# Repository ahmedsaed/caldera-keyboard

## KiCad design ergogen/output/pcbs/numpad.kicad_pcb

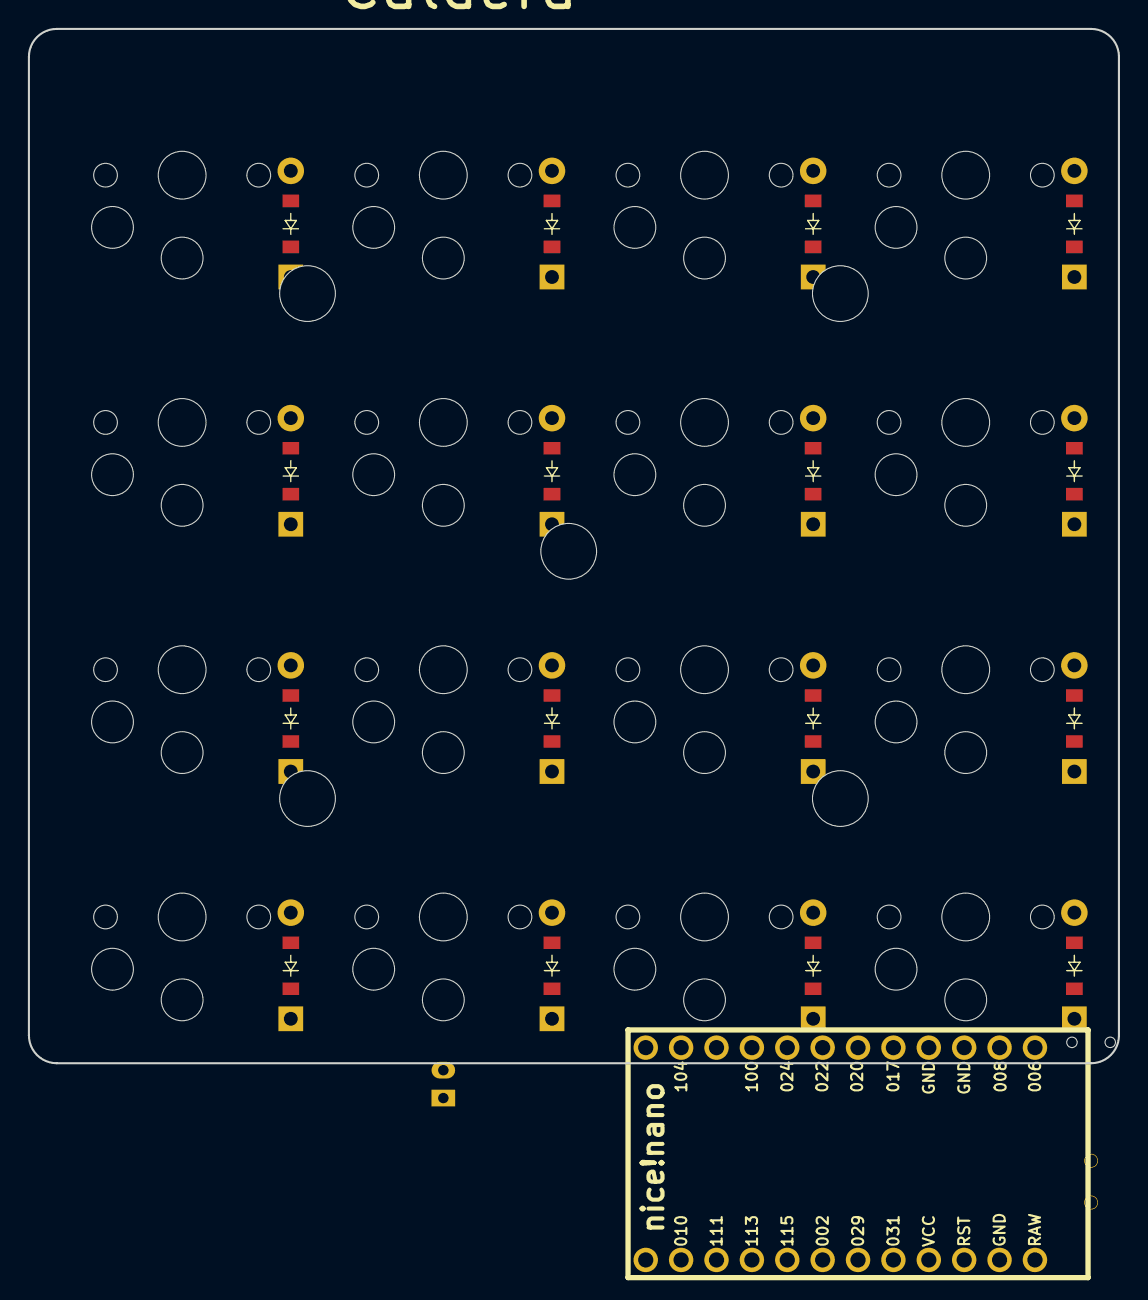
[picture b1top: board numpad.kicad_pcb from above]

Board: 2 copper layers, 78.2 x 74.2 mm, 36 parts (0 on the bottom side), 28 nets, no tracks yet.

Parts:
B1: Panasonic_EVQPUL_EVQPUC
D1, D2, D3, D4, D5, D6, D7, D8, D9, D10, D11, D12, D13, D14, D15, D16: ComboDiode
JST1: JST_PH_S2B-PH-K_02x2.00mm_Angled
MCU1: nice_nano
S1, S2, S3, S4, S5, S6, S7, S8, S9, S10, S11, S12, S13, S14, S15, S16: PG1350
T1: SPDT_C128955

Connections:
GND: B1.1, JST1.2, MCU1.3, MCU1.4, MCU1.23
P002: D3.1, D7.1, D11.1, D15.1, MCU1.18
P020: MCU1.6, S1.1, S2.1, S3.1, S4.1
P022: MCU1.7, S5.1, S6.1, S7.1, S8.1
P024: MCU1.8, S9.1, S10.1, S11.1, S12.1
P029: D4.1, D8.1, D12.1, D16.1, MCU1.19
P100: MCU1.9, S13.1, S14.1, S15.1, S16.1
P113: D1.1, D5.1, D9.1, D13.1, MCU1.16
P115: D2.1, D6.1, D10.1, D14.1, MCU1.17
RAW: MCU1.24, T1.2
RST: B1.2, MCU1.22
col0_row0: D1.2, S1.2
col0_row1: D2.2, S2.2
col0_row2: D3.2, S3.2
col0_row3: D4.2, S4.2
col1_row0: D5.2, S5.2
col1_row1: D6.2, S6.2
col1_row2: D7.2, S7.2
col1_row3: D8.2, S8.2
col2_row0: D9.2, S9.2
col2_row1: D10.2, S10.2
col2_row2: D11.2, S11.2
col2_row3: D12.2, S12.2
col3_row0: D13.2, S13.2
col3_row1: D14.2, S14.2
col3_row2: D15.2, S15.2
col3_row3: D16.2, S16.2
pos: JST1.1, T1.1

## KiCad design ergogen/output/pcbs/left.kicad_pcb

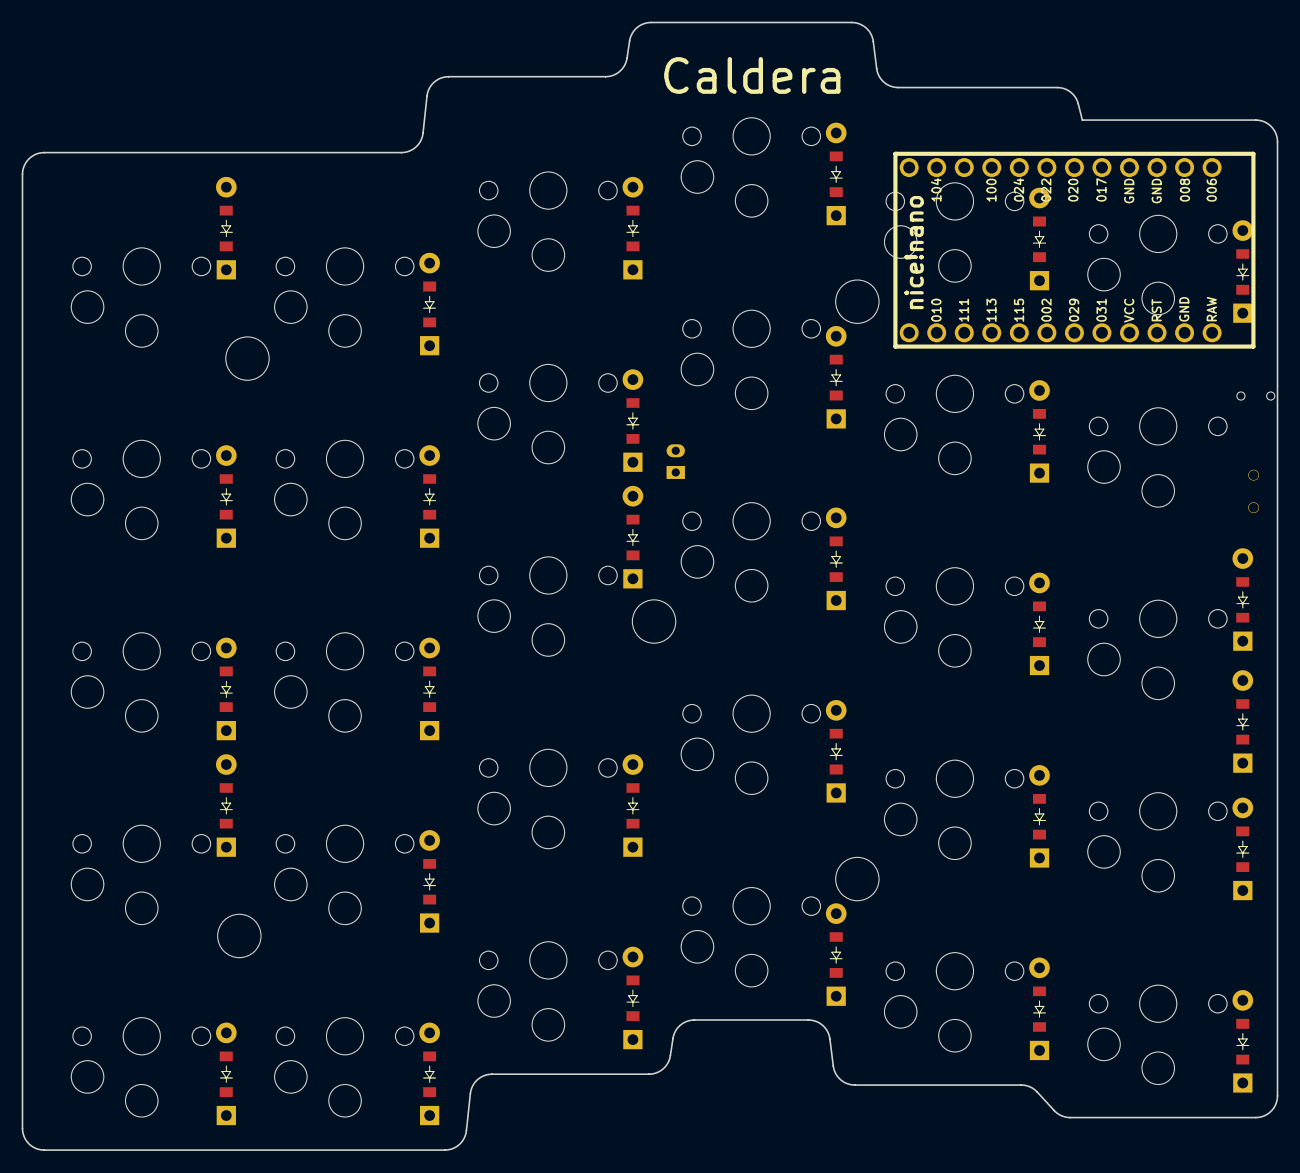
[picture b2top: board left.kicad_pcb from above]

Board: 2 copper layers, 115.8 x 104.0 mm, 64 parts (0 on the bottom side), 45 nets, no tracks yet.

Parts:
B1: Panasonic_EVQPUL_EVQPUC
D1, D2, D3, D4, D5, D6, D7, D8, D9, D10, D11, D12, D13, D14, D15, D16, D17, D18, D19, D20, D21, D22, D23, D24, D25, D26, D27, D28, D29, D30: ComboDiode
JST1: JST_PH_S2B-PH-K_02x2.00mm_Angled
MCU1: nice_nano
S1, S2, S3, S4, S5, S6, S7, S8, S9, S10, S11, S12, S13, S14, S15, S16, S17, S18, S19, S20, S21, S22, S23, S24, S25, S26, S27, S28, S29, S30: PG1350
T1: SPDT_C128955

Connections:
GND: B1.1, JST1.2, MCU1.3, MCU1.4, MCU1.23
P002: D2.1, D6.1, D14.1, D18.1, D25.1, D28.1, MCU1.18
P011: MCU1.10, S21.1, S22.1, S23.1, S24.1, S25.1
P017: MCU1.5, S26.1, S27.1, S28.1, S29.1, S30.1
P020: MCU1.6, S1.1, S2.1, S3.1, S4.1, S5.1
P022: MCU1.7, S6.1, S7.1, S8.1, S9.1, S10.1
P024: MCU1.8, S11.1, S12.1, S13.1, S14.1, S15.1
P029: D3.1, D7.1, D11.1, D19.1, D24.1, D30.1, MCU1.19
P031: D8.1, D12.1, D15.1, D20.1, D23.1, D27.1, MCU1.20
P100: MCU1.9, S16.1, S17.1, S18.1, S19.1, S20.1
P113: D1.1, D4.1, D9.1, D16.1, D21.1, D29.1, MCU1.16
P115: D5.1, D10.1, D13.1, D17.1, D22.1, D26.1, MCU1.17
RAW: MCU1.24, T1.2
RST: B1.2, MCU1.22
fifth_bottom: D17.2, S22.2
fifth_home: D18.2, S23.2
fifth_mod: D16.2, S21.2
fifth_num: D20.2, S25.2
fifth_top: D19.2, S24.2
first_bottom: D26.2, S2.2
first_home: D2.2, S3.2
first_mod: D1.2, S1.2
first_num: D27.2, S5.2
first_top: D3.2, S4.2
fourth_bottom: D13.2, S17.2
fourth_home: D14.2, S18.2
fourth_mod: D29.2, S16.2
fourth_num: D15.2, S20.2
fourth_top: D30.2, S19.2
pos: JST1.1, T1.1
second_bottom: D5.2, S7.2
second_home: D6.2, S8.2
second_mod: D4.2, S6.2
second_num: D8.2, S10.2
second_top: D7.2, S9.2
sixth_bottom: D22.2, S27.2
sixth_home: D25.2, S28.2
sixth_mod: D21.2, S26.2
sixth_num: D23.2, S30.2
sixth_top: D24.2, S29.2
third_bottom: D10.2, S12.2
third_home: D28.2, S13.2
third_mod: D9.2, S11.2
third_num: D12.2, S15.2
third_top: D11.2, S14.2

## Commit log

2025-11-23 restructure
2025-11-23 fix restructuring
2026-02-16 add support for studio RPC and unlock functionality in keymap
2026-02-18 update keymap layout and bindings for improved functionality
2026-02-18 Revert "add support for studio RPC and unlock functionality in keymap"
    This reverts commit fe5547a2458e9b684e012490117596a2e78298dd.
2026-02-18 update high layer key bindings for improved functionality
2026-02-18 update keymap to enhance layer transitions and improve functionality
2026-02-27 fix keymap formatting for consistency in control layer bindings
2026-02-27 fix keymap formatting for consistency in default layer bindings
2026-02-28 update keymap to replace CAPS with HIGH layer and adjust bindings for improved functionality
2026-05-27 Add numpad bottom plate and case design
    - Implemented the bottom plate for the Caldera Numpad, including a rounded rectangle shape, potentiometer housing, and snap clips for secure attachment.
    - Created the case design with walls, snap ridges, and cutouts for switches and a potentiometer, ensuring proper alignment and fit for the components.
2026-05-29 Increase potentiometer hole diameter to accommodate encoder shaft in numpad case design
2026-05-29 Refactor numpad bottom plate to support EC11 encoder housing; add PCB plate for Kailh Choc v1 switches
2026-05-29 Fix pin 2 coordinates in numpad PCB plate design for correct alignment
2026-05-29 Fix ridge orientation in numpad case and adjust PCB plate dimensions
    - Corrected the translation and rotation of the ridge module in numpad_case.scad to ensure proper alignment.
    - Updated the plate thickness and increased the diameter of the leg, post, and pin dimensions in numpad_pcb_plate.scad for improved fit and clearance.
2026-05-30 Refactor numpad dimensions for consistency and accuracy
    - Updated key pitch variables to pitch_x and pitch_y for clarity in numpad_bottom.scad, numpad_case.scad, and numpad_pcb_plate.scad.
    - Adjusted switch cutout size from 13.8 to 14 in numpad_bottom.scad and numpad_case.scad for improved fit.
    - Modified board width and height calculations to use new pitch variables, ensuring correct alignment and spacing.
    - Added USB-C and power switch cutouts in numpad_case.scad for enhanced functionality.
2026-05-30 Adjust PCB plate dimensions for improved fit and clearance
    - Reduced board width and height by 0.2mm for better clearance.
    - Decreased leg diameter to 2.2mm for improved fit.
    - Updated post diameter to 3.6mm for enhanced clearance.
    - Changed pin diameter to 3.1mm to accommodate hot-swap socket leg press-fit.
